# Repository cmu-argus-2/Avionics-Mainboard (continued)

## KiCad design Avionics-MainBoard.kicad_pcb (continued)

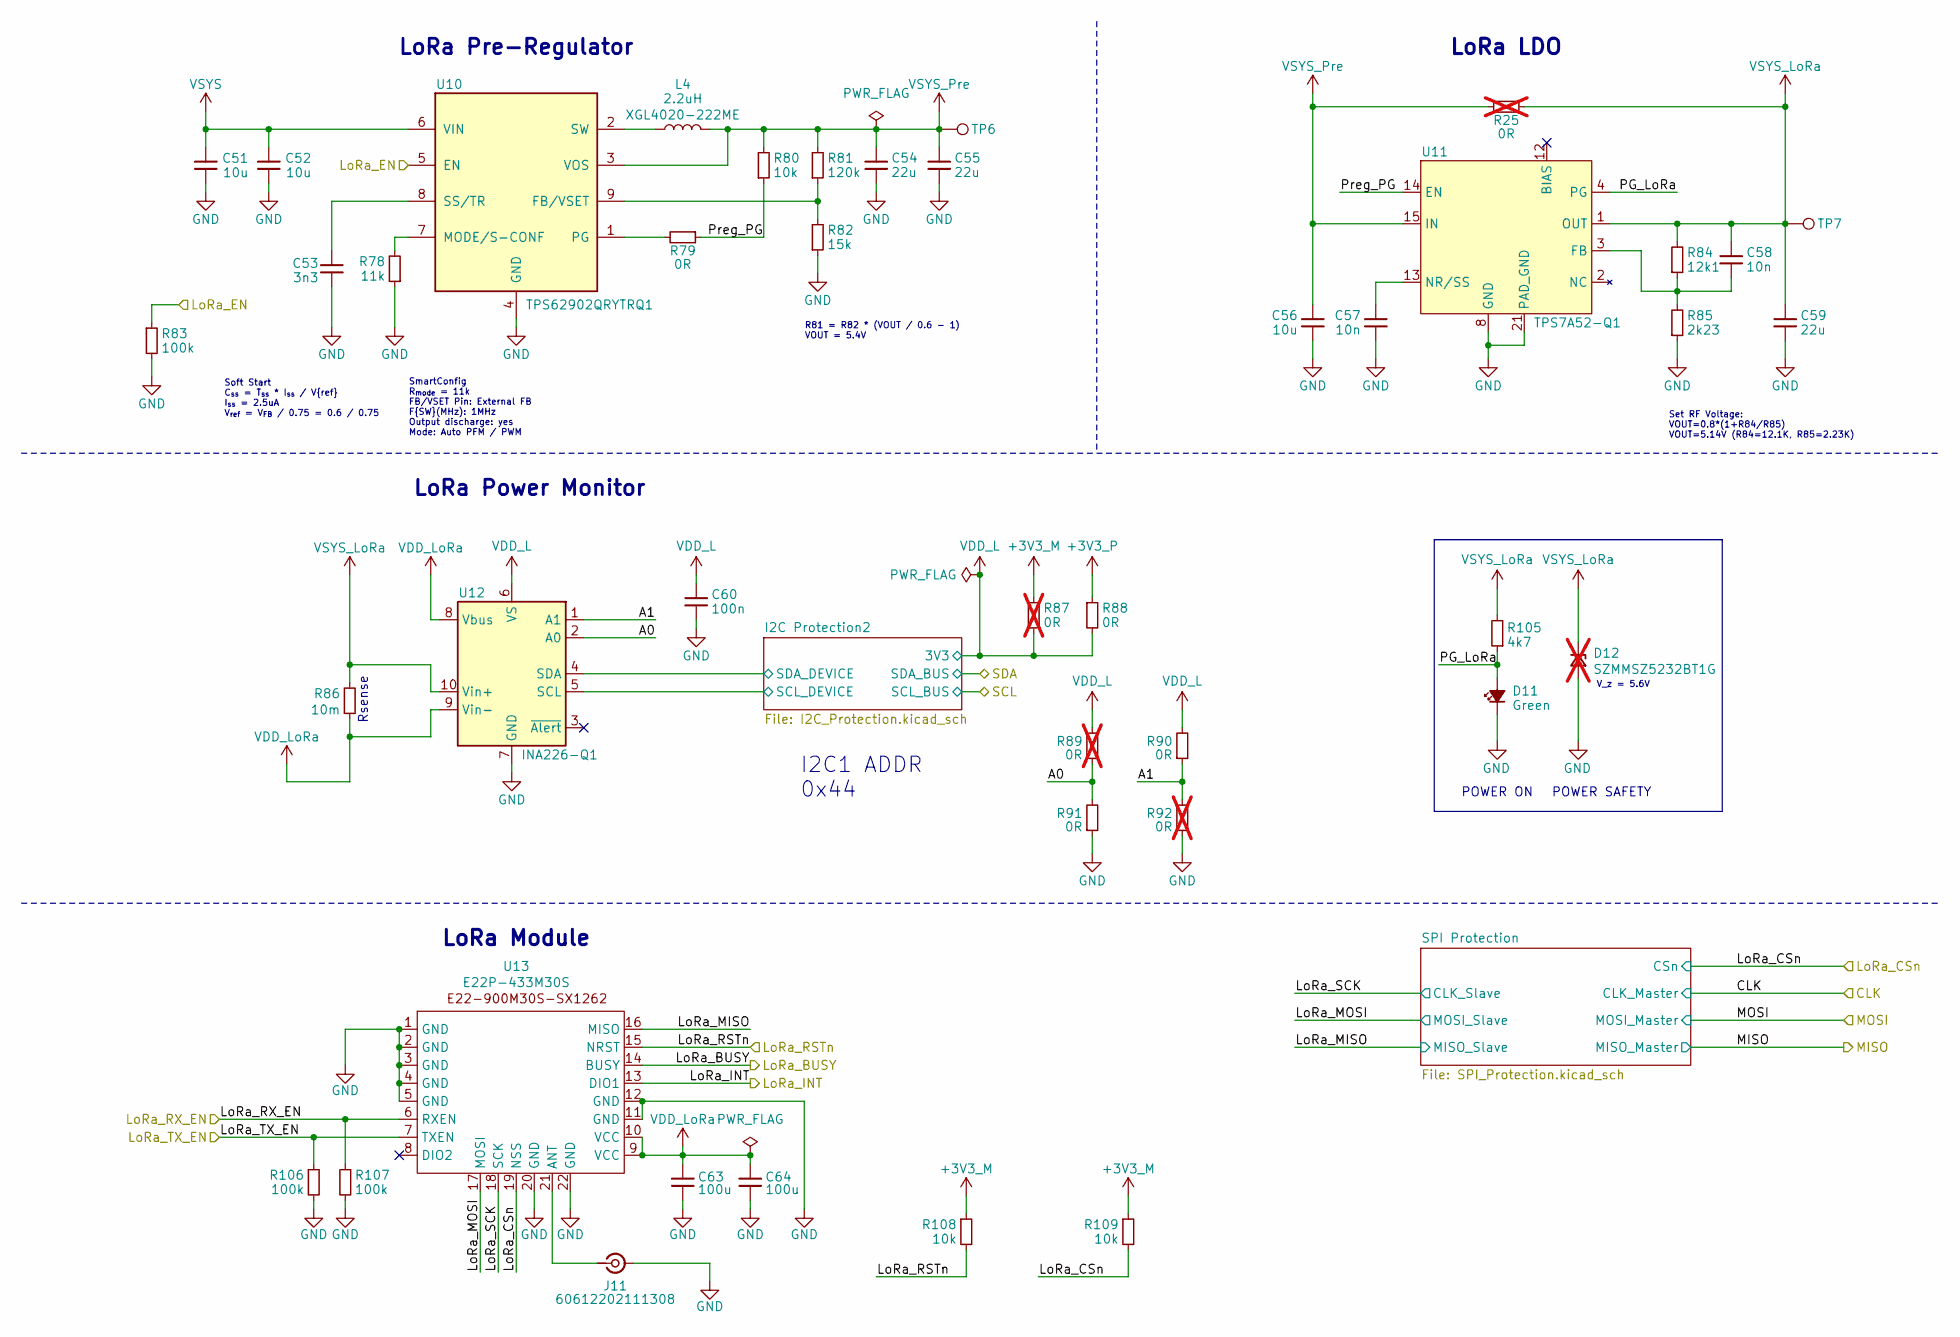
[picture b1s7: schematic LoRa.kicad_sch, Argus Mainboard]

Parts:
C51, C52: 10u; C_0805_2012Metric; MPN C386084
C53: 3n3; C_0603_1608Metric; MPN C3877267
C54, C55, C59: 22u; C_1210_3225Metric; MPN C2803395
C56: 10u; C_0805_2012Metric; MPN C2803395
C57, C58: 10n; C_0603_1608Metric; MPN C2803395
C60: 100n; C_0603_1608Metric; MPN C2803395
C63: 100u; C_1210_3225Metric; MPN C2214844
C64: 100u; C_1210_3225Metric; MPN C386084
D11: LED_G_0603_LTST-C190GKT; LED_0603_1608Metric; MPN C2909774
D12: SZMMSZ5232BT1G; D_SOD-123; not fitted
J11: 60612202111308; MPN C88374
L4: 2.2uH; L_Coilcraft_XAL4020-XXX
R25: 0R; R_0603_1608Metric; MPN C844759; not fitted
R78: 11k; R_0603_1608Metric; MPN C844759
R79: 0R; R_0603_1608Metric; MPN C844759
R80: 10k; R_0603_1608Metric; MPN C844759
R81: 120k; R_0603_1608Metric; MPN C844759
R82: 15k; R_0603_1608Metric; MPN C844759
R83: 100k; R_0603_1608Metric; MPN C237792
R84: 12k1; R_0603_1608Metric; MPN C844759
R85: 2k23; R_0603_1608Metric; MPN C844759
R86: 10m; R_1206_3216Metric; MPN C840621
R87: 0R; R_0603_1608Metric; MPN C237792; not fitted
R88: 0R; R_0603_1608Metric; MPN C237792
R89, R92: 0R; R_0603_1608Metric; MPN C844915; not fitted
R90, R91: 0R; R_0603_1608Metric; MPN C844915
R105: 4k7; R_0603_1608Metric; MPN C844931
R106, R107: 100k; R_0603_1608Metric; MPN C2479067
R108, R109: 10k; R_0603_1608Metric; MPN C2479067
TP6, TP7: TestPoint; TestPoint_Pad_D1.5mm
U10: TPS62902QRYTRQ1
U11: TPS7A52-Q1; TPS7A5201Q
U12: INA226-Q1; TSSOP-10_3x3mm_P0.5mm
U13: E22P-433M30S; E22-900M30S-SX1262

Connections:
+3V3_M: R87.1, R108.1, R109.1; also elsewhere on the board
+3V3_P: R88.1; also elsewhere on the board
/LoRa/A0: R89.1, R91.2, U12.2 (A0)
/LoRa/A1: R90.1, R92.2, U12.1 (A1)
/LoRa/I2C Protection2/SCL_DEVICE: U12.5 (SCL); also elsewhere on the board
/LoRa/I2C Protection2/SDA_DEVICE: U12.4 (SDA); also elsewhere on the board
/LoRa/LoRa_BUSY: U13.14 (BUSY); also elsewhere on the board
/LoRa/LoRa_CSn: R109.2, U13.19 (NSS); also elsewhere on the board
/LoRa/LoRa_INT: U13.13 (DIO1); also elsewhere on the board
/LoRa/LoRa_MISO: U13.16 (MISO); also elsewhere on the board
/LoRa/LoRa_MOSI: U13.17 (MOSI); also elsewhere on the board
/LoRa/LoRa_RSTn: R108.2, U13.15 (NRST); also elsewhere on the board
/LoRa/LoRa_RX_EN: R107.1, U13.6 (RXEN); also elsewhere on the board
/LoRa/LoRa_SCK: U13.18 (SCK); also elsewhere on the board
/LoRa/LoRa_TX_EN: R106.1, U13.7 (TXEN); also elsewhere on the board
/LoRa/PG_LoRa: D11.2 (A), R105.1, U11.4 (PG)
/LoRa/Preg_PG: R79.1, R80.1, U11.14 (EN)
/MCU_IO/LoRa_EN: R83.1, U10.5 (EN); also elsewhere on the board
GND: C51.2, C52.2, C53.1, C54.1, C55.1, C56.1, C57.1, C59.1, C60.1, C63.1, C64.1, D11.1 (K), D12.2 (A), J11.2 (Ext), R78.1, R82.1, R83.2, R85.1, R91.1, R92.1, R106.2, R107.2, U10.4 (GND), U11.8 (GND), U11.18 (GND), U11.21 (PAD_GND), U12.7 (GND), U13.1 (GND), U13.2 (GND), U13.3 (GND), U13.4 (GND), U13.5 (GND), U13.11 (GND), U13.12 (GND), U13.20 (GND), U13.22 (GND); also elsewhere on the board
unnamed: J11.1 (In), U13.21 (ANT)
unnamed: R81.1, R82.2, U10.9 (FB/VSET)
unnamed: R78.2, U10.7 (MODE/S-CONF)
unnamed: R79.2, U10.1 (PG)
unnamed: C53.2, U10.8 (SS/TR)
unnamed: L4.1, U10.2 (SW)
unnamed: C58.1, R84.1, R85.2, U11.3 (FB)
unnamed: C57.2, U11.13 (NR/SS)
VDD_L: C60.2, R87.2, R88.2, R89.2, R90.2, U12.6 (VS); also elsewhere on the board
VDD_LoRa: C63.2, C64.2, R86.1, U12.8 (Vbus), U12.9 (Vin-), U13.9 (VCC), U13.10 (VCC)
VSYS: C51.1, C52.1, U10.6 (VIN); also elsewhere on the board
VSYS_LoRa: C58.2, C59.2, D12.1 (K), R25.1, R84.2, R86.2, R105.2, TP7.1 (1_1), U11.1 (OUT), U11.19 (OUT), U11.20 (OUT), U12.10 (Vin+)
VSYS_Pre: C54.2, C55.2, C56.2, L4.2, R25.2, R80.2, R81.2, TP6.1 (1_1), U10.3 (VOS), U11.15 (IN), U11.16 (IN), U11.17 (IN)

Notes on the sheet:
I2C1 ADDR 0x44
R81 = R82 * (VOUT / 0.6 - 1) VOUT = 5.4V
LoRa Module
LoRa Pre-Regulator
POWER ON
Set RF Voltage: VOUT=0.8*(1+R84/R85) VOUT=5.14V (R84=12.1K, R85=2.23K)
SmartConfig R_{mode} = 11k FB/VSET Pin: External FB F{SW}(MHz): 1MHz Output discharge: yes Mode: Auto PFM / PWM
LoRa Power Monitor
V_z = 5.6V
LoRa LDO
Soft Start C_{ss} = T_{ss} * I_{ss} / V{ref} I_{ss} = 2.5uA V_{ref} = V_{FB} / 0.75 = 0.6 / 0.75
POWER SAFETY
Rsense

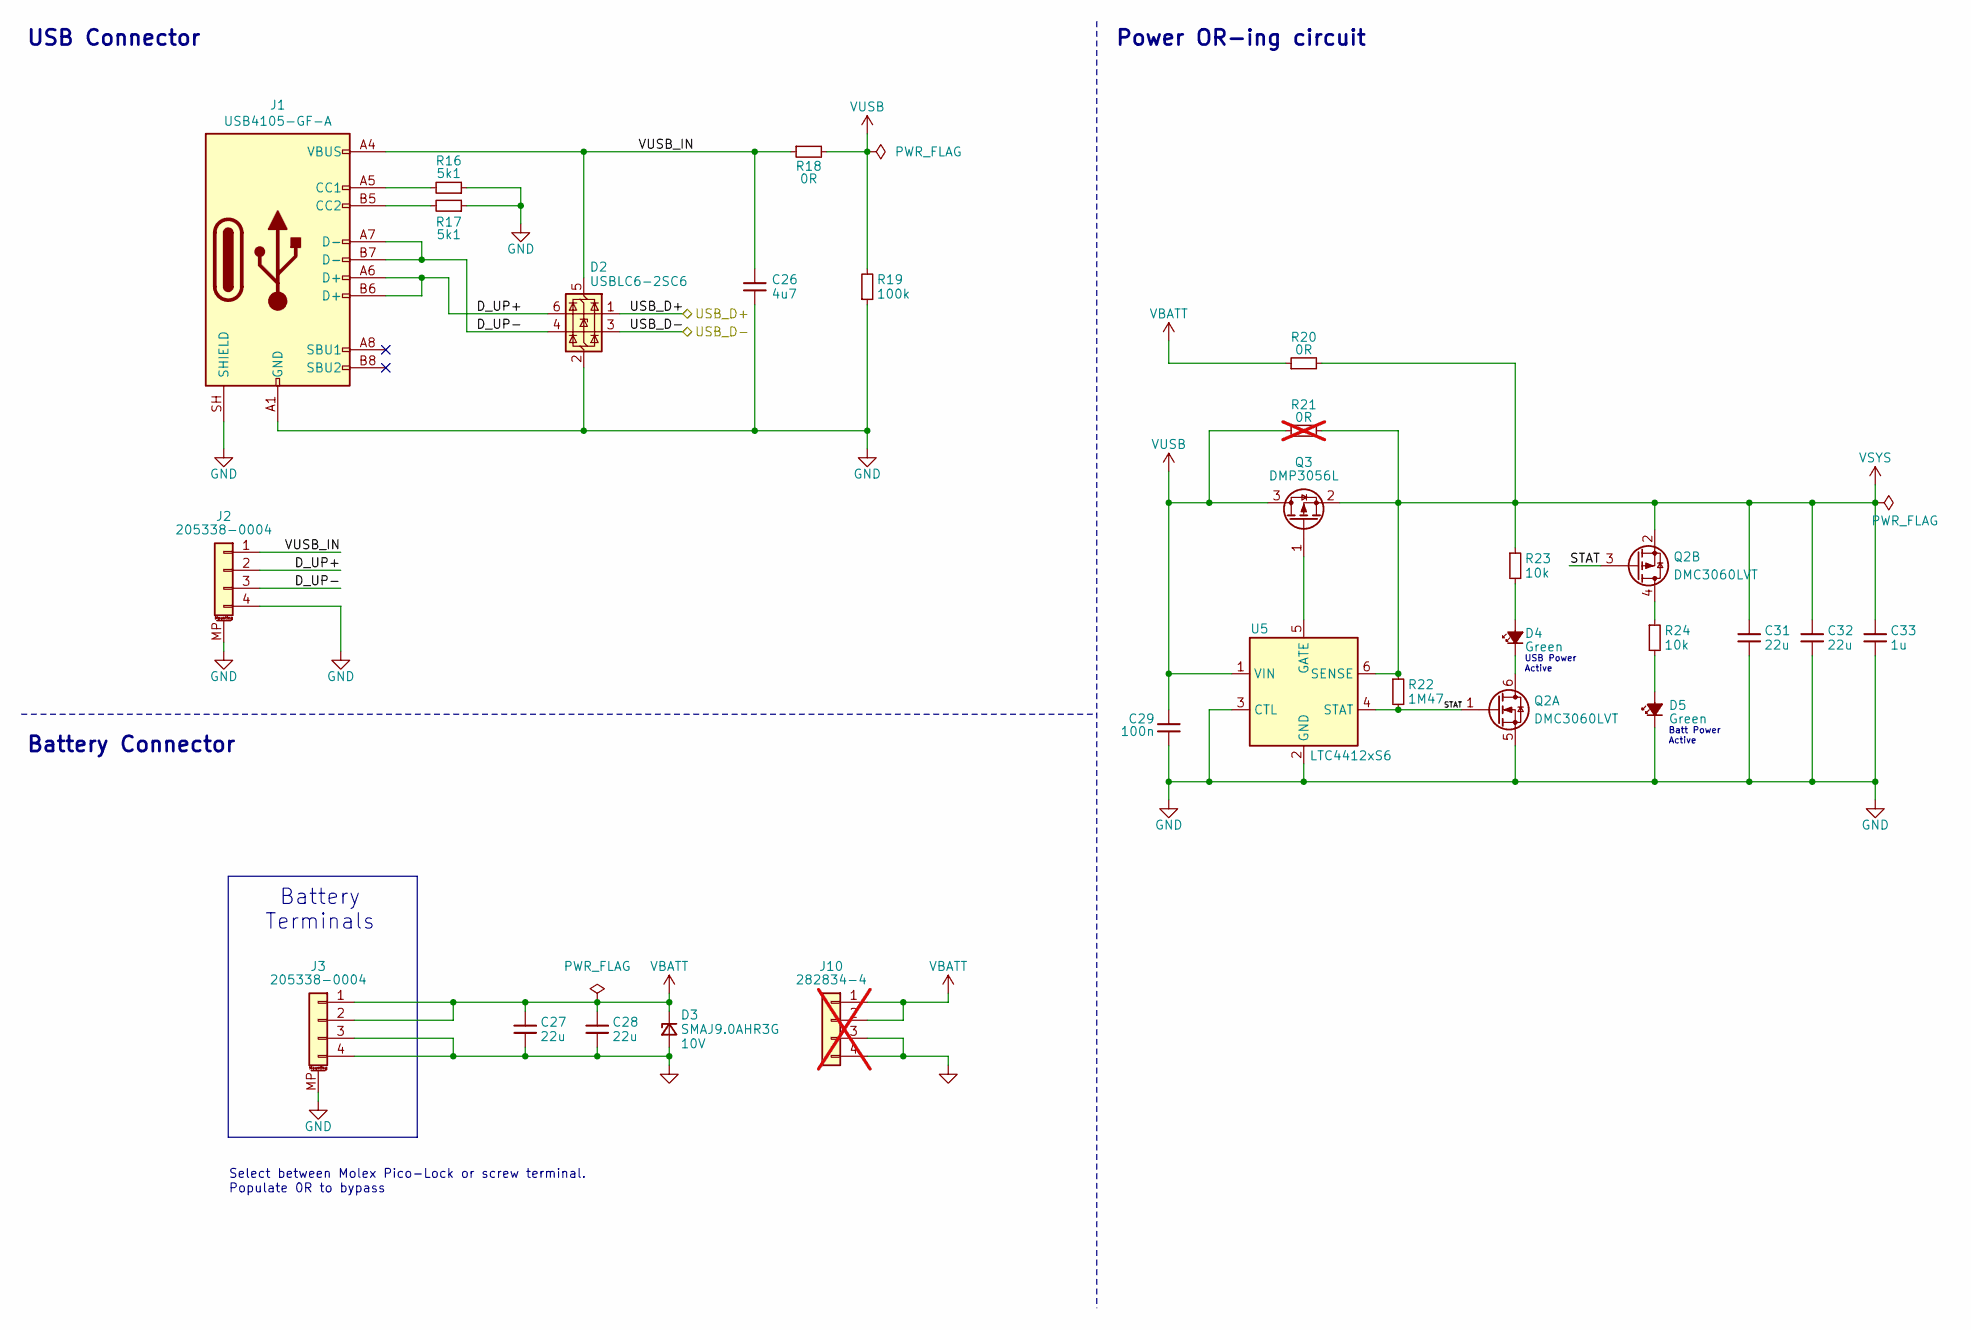
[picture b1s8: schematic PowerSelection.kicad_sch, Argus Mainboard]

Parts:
C26: 4u7; C_0805_2012Metric; MPN C3861036
C27, C28, C31, C32: 22u; C_1210_3225Metric; MPN C2803395
C29: 100n; C_0603_1608Metric; MPN C386084
C33: 1u; C_0603_1608Metric; MPN C2214844
D2: USBLC6-2SC6; SOT-23-6; MPN C7519
D3: SMAJ9.0AHR3G; D_SMA; Part 10V
D4, D5: LED_G_0603_LTST-C190GKT; LED_0603_1608Metric; MPN C2909774
J1: USB4105-GF-A; USB_C_Receptacle_GCT_USB4105-xx-A_16P_TopMnt_Horizontal; MPN C3020560
J2, J3: 205338-0004; Molex_Pico-Lock_205338-0004_1x04-1MP_P2.00mm_Horizontal; MPN C916325
J10: 282834-4; TE_282834-4; not fitted
Q2: DMC3060LVT; TSOT-23-6
Q3: DMP3056L; SOT-23
R16, R17: 5k1; R_0603_1608Metric; MPN C2484686
R18, R20: 0R; R_0603_1608Metric; MPN C844915
R19: 100k; R_0603_1608Metric; MPN C2479067
R21: 0R; R_0603_1608Metric; MPN C844915; not fitted
R22: 1M47; R_0603_1608Metric; MPN C237792
R23, R24: 10k; R_0603_1608Metric; MPN C237792
U5: LTC4412xS6; TSOT-23-6

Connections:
/Power Selection/D_UP+: D2.6 (I/O1), J1.A6 (D+), J1.B6 (D+), J2.2
/Power Selection/D_UP-: D2.4 (I/O2), J1.A7 (D-), J1.B7 (D-), J2.3
/Power Selection/STAT: Q2.1 (G), Q2.3 (G), R22.2, U5.4 (STAT)
/Power Selection/USB_D+: D2.1 (I/O1); also elsewhere on the board
/Power Selection/USB_D-: D2.3 (I/O2); also elsewhere on the board
/Power Selection/VUSB_IN: C26.1, D2.5 (VBUS), J1.A4 (VBUS), J1.A9 (VBUS), J1.B4 (VBUS), J1.B9 (VBUS), J2.1, R18.1
GND: C26.2, C27.2, C28.2, C29.1, C31.1, C32.1, C33.2, D2.2 (GND), D3.2 (A), D5.1 (K), J1.A1 (GND), J1.A12 (GND), J1.B1 (GND), J1.B12 (GND), J1.SH (SHIELD), J2.4, J2.MP (MountPin), J3.3, J3.4, J3.MP (MountPin), J10.3, J10.4, Q2.5 (S), R16.1, R17.1, R19.1, U5.2 (GND), U5.3 (CTL); also elsewhere on the board
unnamed: D4.2 (A), R23.2
unnamed: D4.1 (K), Q2.6 (D)
unnamed: D5.2 (A), R24.2
unnamed: J1.A5 (CC1), R16.2
unnamed: J1.B5 (CC2), R17.2
unnamed: Q2.4 (D), R24.1
unnamed: Q3.1 (G), U5.5 (GATE)
VBATT: C27.1, C28.1, D3.1 (K), J3.1, J3.2, J10.1, J10.2, R20.1; also elsewhere on the board
VSYS: C31.2, C32.2, C33.1, Q2.2 (S), Q3.2 (S), R20.2, R21.2, R22.1, R23.1, U5.6 (SENSE); also elsewhere on the board
VUSB: C29.2, Q3.3 (D), R18.2, R19.2, R21.1, U5.1 (VIN)

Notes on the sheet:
Batt Power Active
Power OR-ing circuit
Battery Connector
Select between Molex Pico-Lock or screw terminal. Populate 0R to bypass
USB Power Active
USB Connector
Battery Terminals

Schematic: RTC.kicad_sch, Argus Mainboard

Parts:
BT2: BAT-HLD-012-SMT; BatteryHolder_LINX_BAT-HLD-012-SMT; MPN C5189234
C75, C76: 10u; C_0805_2012Metric; MPN C307348
C77, C78: 100n; C_0603_1608Metric; MPN C307348
D16: LED_G_0603_LTST-C190GKT; LED_0603_1608Metric; MPN C2909774
R138, R140: 0R; R_0603_1608Metric; not fitted
R139: 0R; R_0603_1608Metric
R141, R144: 100k; R_0603_1608Metric
R142: 2k7; R_0603_1608Metric; MPN C237112
R143: 10k; R_0603_1608Metric
R185: 10k; R_0603_1608Metric; MPN C237112
TP8: TestPoint; TestPoint_Pad_D1.5mm
U17: TPS22917DBV; SOT-23-6
U18: RV-3032-C7; IC_RV-3032-C7-32.768KHZ-2.5PPM-TA-QC

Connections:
+3V3_M: R138.1, R143.1; also elsewhere on the board
+3V3_P: R139.1; also elsewhere on the board
+3V3_RTC: C76.1, C77.1, R140.1, R142.2, R185.2, U17.6 (VOUT), U18.6 (VDD); also elsewhere on the board
/MCU_IO/RTC_EN: R141.1, U17.3 (ON); also elsewhere on the board
/MCU_IO/RTC_INT: R143.2, U18.3 (~INT); also elsewhere on the board
/RTC/EVI: R144.1, U18.4 (EVI)
/RTC/RTC_SCL: U18.8 (SCL); also elsewhere on the board
/RTC/RTC_SDA: U18.2 (SDA); also elsewhere on the board
GND: BT2.2 (-), C75.2, C76.2, C77.2, C78.2, D16.1 (K), R141.2, R144.2, U17.2 (GND), U18.5 (VSS); also elsewhere on the board
unnamed: BT2.1 (+), C78.1, U18.1 (VBACKUP)
unnamed: D16.2 (A), R142.1
unnamed: R185.1, U17.5 (QOD)
unnamed: C75.1, R138.2, R139.2, R140.2, U17.1 (VIN)
unnamed: TP8.1 (1_1), U18.7 (CLKOUT)

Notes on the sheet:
RTC Enable
I2C1 ADDR 0x51
RTC

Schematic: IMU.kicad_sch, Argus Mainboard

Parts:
C81, C82, C83, C85, C86: 10u; C_0805_2012Metric; MPN C307348
C84: 1u; C_0603_1608Metric; MPN C307348
C87, C88: 100n; C_0603_1608Metric; MPN C307348
D17, D18: LED_G_0603_LTST-C190GKT; LED_0603_1608Metric; MPN C2909774
R157, R159, R169, R171: 0R; R_0603_1608Metric; not fitted
R158, R170: 0R; R_0603_1608Metric
R160, R172: 100k; R_0603_1608Metric
R161, R173: 2k7; R_0603_1608Metric; MPN C237112
R162, R174: 10k; R_0603_1608Metric; MPN C2479067
R163, R175, R176: 100k; R_0603_1608Metric; MPN C2479067
R183, R184: 10k; R_0603_1608Metric; MPN C237112
U19, U21: TPS22917DBV; SOT-23-6
U20: MMC5983MA; LGA-16_3x3mm_P0.5mm
U22: ASM330LHHG1TR; LGA-14_3x2.5mm_P0.5mm_LayoutBorder3x4y

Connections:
+3V3_IMU: C86.1, C87.1, C88.1, R171.1, R173.2, R174.2, R184.2, U21.6 (VOUT), U22.5 (VDDIO), U22.8 (VDD)
+3V3_M: R157.1, R169.1; also elsewhere on the board
+3V3_MAG: C82.1, C84.1, R159.1, R161.2, R162.2, R183.2, U19.6 (VOUT), U20.2 (VDD), U20.13 (VDDIO)
+3V3_P: R158.1, R170.1; also elsewhere on the board
/IMU/IMU_CSn: R174.1, U22.12 (CS); also elsewhere on the board
/IMU/IMU_INT1: R175.2, U22.4 (INT1); also elsewhere on the board
/IMU/IMU_INT2: R176.2, U22.9 (INT2); also elsewhere on the board
/IMU/IMU_MISO: U22.1 (SDO/SA0); also elsewhere on the board
/IMU/IMU_MOSI: U22.14 (SDA); also elsewhere on the board
/IMU/IMU_SCK: U22.13 (SCL); also elsewhere on the board
/IMU/Mag_CSn: R162.1, U20.4 (CS); also elsewhere on the board
/IMU/Mag_INT: R163.1, U20.15 (INT); also elsewhere on the board
/IMU/Mag_MISO: U20.5 (MISO); also elsewhere on the board
/IMU/Mag_MOSI: U20.16 (MOSI); also elsewhere on the board
/IMU/Mag_SCK: U20.1 (SCK); also elsewhere on the board
/MCU_IO/IMU_EN: R172.1, U21.3 (ON); also elsewhere on the board
/MCU_IO/Mag_EN: R160.1, U19.3 (ON); also elsewhere on the board
GND: C81.2, C82.2, C83.2, C84.2, C85.2, C86.2, C87.2, C88.2, D17.1 (K), D18.1 (K), R160.2, R163.2, R172.2, R175.1, R176.1, U19.2 (GND), U20.9 (GND), U20.11 (GND), U21.2 (GND), U22.2 (SDx), U22.3 (SCx), U22.6 (GND), U22.7 (GND); also elsewhere on the board
unnamed: D17.2 (A), R161.1
unnamed: D18.2 (A), R173.1
unnamed: R183.1, U19.5 (QOD)
unnamed: C81.1, R157.2, R158.2, R159.2, U19.1 (VIN)
unnamed: C83.1, U20.10 (CAP)
unnamed: R184.1, U21.5 (QOD)
unnamed: C85.1, R169.2, R170.2, R171.2, U21.1 (VIN)

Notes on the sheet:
Magnetometer
6-DoF IMU (Accelerometer + Gyroscope)

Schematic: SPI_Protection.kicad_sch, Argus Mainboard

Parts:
Q24: MMBT2907; SOT-23; MPN C5354954
R164: 4k7; R_0603_1608Metric; MPN C844931
R165: 0R; R_0603_1608Metric; MPN C844915
R166, R167: 1k; R_0603_1608Metric; MPN C2484712
R168: 0R; R_0603_1608Metric; not fitted

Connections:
/IMU/CLK: R166.2; also elsewhere on the board
/IMU/MISO: Q24.3 (C), R168.1; also elsewhere on the board
/IMU/MOSI: R167.2; also elsewhere on the board
/IMU/Mag_CSn: R164.2; also elsewhere on the board
/IMU/Mag_MISO: R165.2, R168.2; also elsewhere on the board
/IMU/Mag_MOSI: R167.1; also elsewhere on the board
/IMU/Mag_SCK: R166.1; also elsewhere on the board
unnamed: Q24.1 (B), R164.1
unnamed: Q24.2 (E), R165.1

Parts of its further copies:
Q18, Q19, Q25: MMBT2907; SOT-23; MPN C5354954
R110, R133, R177: 4k7; R_0603_1608Metric; MPN C844931
R111, R134, R178: 0R; R_0603_1608Metric; MPN C844915
R112, R113, R135, R136, R179, R180: 1k; R_0603_1608Metric; MPN C2484712
R114, R137, R181: 0R; R_0603_1608Metric; not fitted

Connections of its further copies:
/IMU/CLK: R112.2, R135.2, R179.2; also elsewhere on the board
/IMU/IMU_CSn: R177.2; also elsewhere on the board
/IMU/IMU_MISO: R178.2, R181.2; also elsewhere on the board
/IMU/IMU_MOSI: R180.1; also elsewhere on the board
/IMU/IMU_SCK: R179.1; also elsewhere on the board
/IMU/MISO: Q18.3 (C), Q19.3 (C), Q25.3 (C), R114.1, R137.1, R181.1; also elsewhere on the board
/IMU/MOSI: R113.2, R136.2, R180.2; also elsewhere on the board
/LoRa/LoRa_CSn: R110.2; also elsewhere on the board
/LoRa/LoRa_MISO: R111.2, R114.2; also elsewhere on the board
/LoRa/LoRa_MOSI: R113.1; also elsewhere on the board
/LoRa/LoRa_SCK: R112.1; also elsewhere on the board
/MCU_IO/SD_CSn: R133.2; also elsewhere on the board
/SD/SD_CLK: R135.1; also elsewhere on the board
/SD/SD_MISO: R134.2, R137.2; also elsewhere on the board
/SD/SD_MOSI: R136.1; also elsewhere on the board
unnamed: Q18.1 (B), R110.1
unnamed: Q18.2 (E), R111.1
unnamed: Q19.1 (B), R133.1
unnamed: Q19.2 (E), R134.1
unnamed: Q25.1 (B), R177.1
unnamed: Q25.2 (E), R178.1

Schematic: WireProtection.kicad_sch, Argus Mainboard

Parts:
C40: 10n; C_0603_1608Metric; MPN C161232
Q4: MBT2222ADW1T1; SOT-363_SC-70-6; Manufacturer_Part_Number MBT2222ADW1T1G
Q5: NX3008NBKS; SOT-363_SC-70-6; MPN C3280240
R36, R37: 10k; R_0603_1608Metric; MPN C2479067
R38: 680R; R_0603_1608Metric; MPN C844802
R39: 100k; R_0603_1608Metric; MPN C237792
R40: 200k; R_0603_1608Metric; MPN C118142
R41: 0R; R_0603_1608Metric; not fitted

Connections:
/MCU_IO/I2C0_SCL: Q4.1 (E1), Q4.3 (C2), R41.2; also elsewhere on the board
/Main Power/I2C Protection/SCL_DEVICE: Q4.4 (E2), Q4.6 (C1), R37.2, R40.1, R41.1; also elsewhere on the board
GND: C40.2, Q5.1 (S), Q5.4 (S); also elsewhere on the board
unnamed: Q4.2 (B1), R38.1
unnamed: Q4.5 (B2), Q5.6 (D), R36.2, R38.2
unnamed: Q5.2 (G), Q5.3 (D), R39.2
unnamed: C40.1, Q5.5 (G), R40.2
VDD_M: R36.1, R37.1, R39.1; also elsewhere on the board

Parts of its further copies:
C41, C48, C49, C61, C62, C79, C80: 10n; C_0603_1608Metric; MPN C161232
Q6, Q8, Q10, Q14, Q16, Q20, Q22: MBT2222ADW1T1; SOT-363_SC-70-6; Manufacturer_Part_Number MBT2222ADW1T1G
Q7, Q9, Q11, Q15, Q17, Q21, Q23: NX3008NBKS; SOT-363_SC-70-6; MPN C3280240
R42, R43, R58, R59, R64, R65, R93, R94, R99, R100, R145, R146, R151, R152: 10k; R_0603_1608Metric; MPN C2479067
R44, R60, R66, R95, R101, R147, R153: 680R; R_0603_1608Metric; MPN C844802
R45, R61, R67, R96, R102, R148, R154: 100k; R_0603_1608Metric; MPN C237792
R46, R62, R68, R97, R103, R149, R155: 200k; R_0603_1608Metric; MPN C118142
R47, R63, R69, R98, R104, R150, R156: 0R; R_0603_1608Metric; not fitted

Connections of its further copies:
+3V3_RTC: R145.1, R146.1, R148.1, R151.1, R152.1, R154.1; also elsewhere on the board
/LoRa/I2C Protection2/SCL_DEVICE: Q14.4 (E2), Q14.6 (C1), R94.2, R97.1, R98.1; also elsewhere on the board
/LoRa/I2C Protection2/SDA_DEVICE: Q16.4 (E2), Q16.6 (C1), R100.2, R103.1, R104.1; also elsewhere on the board
/MCU_IO/I2C0_SCL: Q8.1 (E1), Q8.3 (C2), Q14.1 (E1), Q14.3 (C2), Q20.1 (E1), Q20.3 (C2), R63.2, R98.2, R150.2; also elsewhere on the board
/MCU_IO/I2C0_SDA: Q6.1 (E1), Q6.3 (C2), Q10.1 (E1), Q10.3 (C2), Q16.1 (E1), Q16.3 (C2), Q22.1 (E1), Q22.3 (C2), R47.2, R69.2, R104.2, R156.2; also elsewhere on the board
/Main Power/I2C Protection1/SCL_DEVICE: Q8.4 (E2), Q8.6 (C1), R59.2, R62.1, R63.1; also elsewhere on the board
/Main Power/I2C Protection1/SDA_DEVICE: Q10.4 (E2), Q10.6 (C1), R65.2, R68.1, R69.1; also elsewhere on the board
/Main Power/I2C Protection/SDA_DEVICE: Q6.4 (E2), Q6.6 (C1), R43.2, R46.1, R47.1; also elsewhere on the board
/RTC/RTC_SCL: Q20.4 (E2), Q20.6 (C1), R146.2, R149.1, R150.1; also elsewhere on the board
/RTC/RTC_SDA: Q22.4 (E2), Q22.6 (C1), R152.2, R155.1, R156.1; also elsewhere on the board
GND: C41.2, C48.2, C49.2, C61.2, C62.2, C79.2, C80.2, Q7.1 (S), Q7.4 (S), Q9.1 (S), Q9.4 (S), Q11.1 (S), Q11.4 (S), Q15.1 (S), Q15.4 (S), Q17.1 (S), Q17.4 (S), Q21.1 (S), Q21.4 (S), Q23.1 (S), Q23.4 (S); also elsewhere on the board
unnamed: Q6.2 (B1), R44.1
unnamed: Q6.5 (B2), Q7.6 (D), R42.2, R44.2
unnamed: Q7.2 (G), Q7.3 (D), R45.2
unnamed: C41.1, Q7.5 (G), R46.2
unnamed: Q8.2 (B1), R60.1
unnamed: Q8.5 (B2), Q9.6 (D), R58.2, R60.2
unnamed: Q9.2 (G), Q9.3 (D), R61.2
unnamed: C48.1, Q9.5 (G), R62.2
unnamed: Q10.2 (B1), R66.1
unnamed: Q10.5 (B2), Q11.6 (D), R64.2, R66.2
unnamed: Q11.2 (G), Q11.3 (D), R67.2
unnamed: C49.1, Q11.5 (G), R68.2
unnamed: Q14.2 (B1), R95.1
unnamed: Q14.5 (B2), Q15.6 (D), R93.2, R95.2
unnamed: Q15.2 (G), Q15.3 (D), R96.2
unnamed: C61.1, Q15.5 (G), R97.2
unnamed: Q16.2 (B1), R101.1
unnamed: Q16.5 (B2), Q17.6 (D), R99.2, R101.2
unnamed: Q17.2 (G), Q17.3 (D), R102.2
unnamed: C62.1, Q17.5 (G), R103.2
unnamed: Q20.2 (B1), R147.1
unnamed: Q20.5 (B2), Q21.6 (D), R145.2, R147.2
unnamed: Q21.2 (G), Q21.3 (D), R148.2
unnamed: C79.1, Q21.5 (G), R149.2
unnamed: Q22.2 (B1), R153.1
unnamed: Q22.5 (B2), Q23.6 (D), R151.2, R153.2
unnamed: Q23.2 (G), Q23.3 (D), R154.2
unnamed: C80.1, Q23.5 (G), R155.2
VDD_L: R93.1, R94.1, R96.1, R99.1, R100.1, R102.1; also elsewhere on the board
VDD_M: R42.1, R43.1, R45.1; also elsewhere on the board
VDD_P: R58.1, R59.1, R61.1, R64.1, R65.1, R67.1; also elsewhere on the board

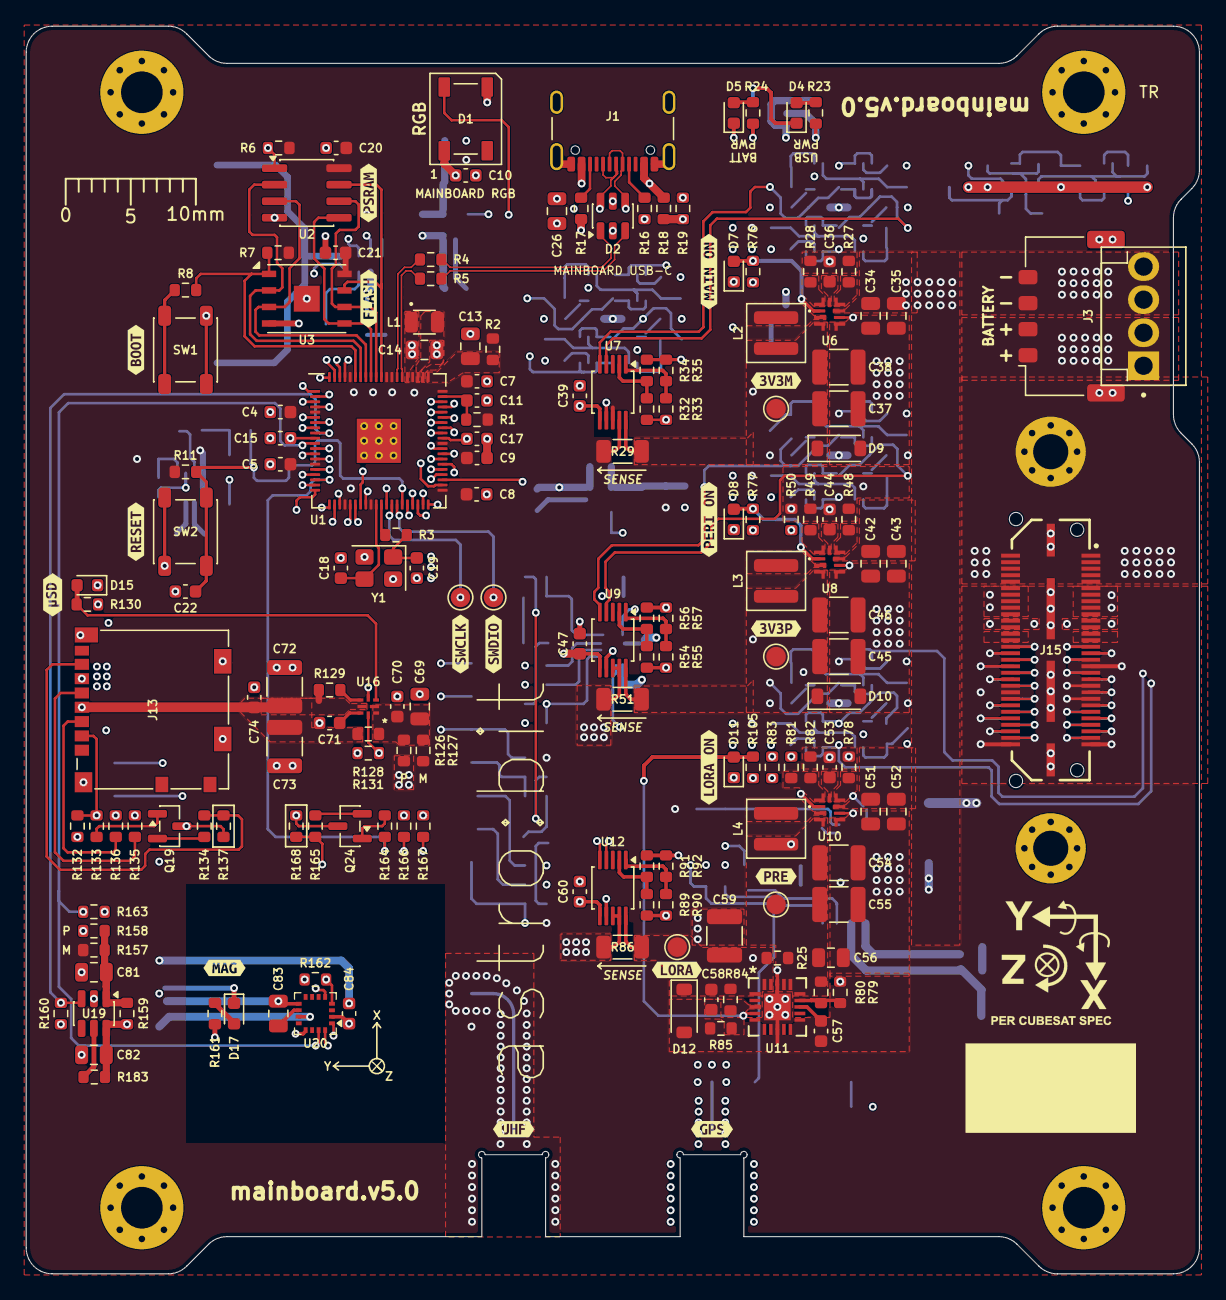
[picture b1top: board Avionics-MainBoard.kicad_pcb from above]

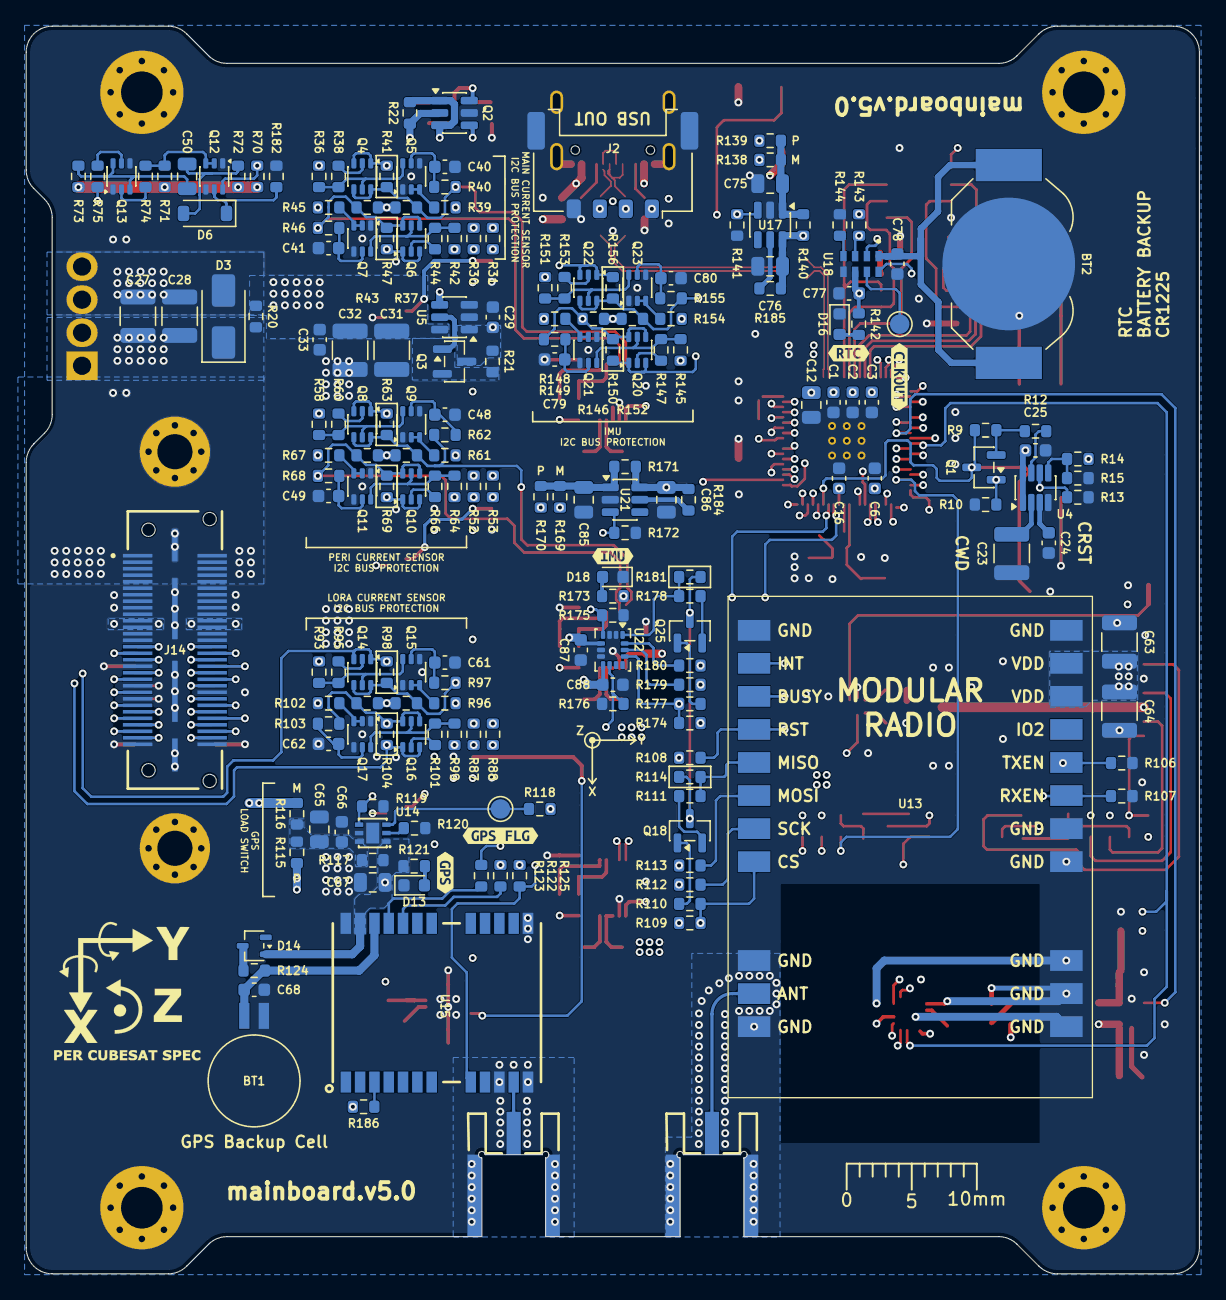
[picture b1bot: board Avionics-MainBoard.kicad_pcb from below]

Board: 4 copper layers, 90.2 x 95.9 mm, 391 parts (202 on the bottom side), 230 nets.

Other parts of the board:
kibuzzard-6A94A6EB: G***; kibuzzard-6A94A6EB
kibuzzard-6A94A6F2: G***; kibuzzard-6A94A6F2
kibuzzard-6A94A9F0: G***; kibuzzard-6A94A9F0
kibuzzard-6A94A74C: G***; kibuzzard-6A94A74C
kibuzzard-6A94A84D: G***; kibuzzard-6A94A84D
kibuzzard-6A94A845: G***; kibuzzard-6A94A845
kibuzzard-6A94A973: G***; kibuzzard-6A94A973
kibuzzard-6A94AA08: G***; kibuzzard-6A94AA08
kibuzzard-6A94AA93: G***; kibuzzard-6A94AA93
kibuzzard-6A94AAA8: G***; kibuzzard-6A94AAA8
kibuzzard-6A94AF59: G***; kibuzzard-6A94AF59
kibuzzard-6A94B7E3: G***; kibuzzard-6A94B7E3
kibuzzard-6A94B390: G***; kibuzzard-6A94B390
kibuzzard-6A94B568: G***; kibuzzard-6A94B568
kibuzzard-6A94B807: G***; kibuzzard-6A94B807
kibuzzard-67C0A908: G***; kibuzzard-67C0A908
kibuzzard-67C0B8D2: G***; kibuzzard-67C0B8D2
kibuzzard-67C0B8E2: G***; kibuzzard-67C0B8E2
kibuzzard-67C0B43D: G***; kibuzzard-67C0B43D
kibuzzard-67C0B44F: G***; kibuzzard-67C0B44F
kibuzzard-67C0B466: G***; kibuzzard-67C0B466
kibuzzard-67C0B482: G***; kibuzzard-67C0B482

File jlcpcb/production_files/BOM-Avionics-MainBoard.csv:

Comment,Designator,Footprint,LCSC,Quantity
0R,"R111,R115,R12,R122,R123,R126,R134,R139,R14,R158,R165,R170,R178,R18,R186,R20,R31,R34,R35,R53,R54,R57,R79,R88,R90,R91",R_0603_1608Metric,C2441282,26
100k,"R10,R102,R106,R107,R119,R129,R131,R141,R144,R148,R154,R160,R163,R172,R175,R176,R182,R19,R39,R45,R50,R61,R67,R71,R73,R83,R96",R_0603_1608Metric,C237792,27
100n,"C1,C10,C15,C16,C17,C2,C20,C21,C25,C29,C3,C39,C4,C47,C5,C6,C60,C66,C7,C74,C77,C78,C8,C87,C88,C9",C_0603_1608Metric,C15725,26
100n,C23,C_1210_3225Metric,C2179848,1
100u,"C63,C64",C_1210_3225Metric,C394395,2
104031-0811,J13,microSD_HC_Molex_104031-0811,C585350,1
10R,R2,R_0603_1608Metric,C2479145,1
10k,"R100,R108,R109,R11,R118,R125,R13,R132,R143,R145,R146,R151,R152,R162,R174,R183,R184,R185,R23,R24,R36,R37,R42,R43,R58,R59,R6,R64,R65,R7,R75,R80,R93,R94,R99",R_0603_1608Metric,C2479067,35
10m,"R29,R51,R86",R_1206_3216Metric,C844280,3
10n,"C24,C40,C41,C48,C49,C57,C58,C61,C62,C79,C80",C_0603_1608Metric,C1589,11
10u,"C34,C35,C42,C43,C50,C51,C52,C56,C65,C67,C69,C75,C76,C81,C82,C83,C85,C86",C_0805_2012Metric,C15850,18
11k,R78,R_0603_1608Metric,C2479538,1
120k,R81,R_0603_1608Metric,C844735,1
12k1,R84,R_0603_1608Metric,C2483996,1
15k,R82,R_0603_1608Metric,C6112657,1
15p,"C18,C19",C_0603_1608Metric,C1644,2
1M47,R22,R_0603_1608Metric,C407542,1
1N4148W,D6,D_SOD-123,C83528,1
1k,"R112,R113,R124,R135,R136,R166,R167,R179,R180,R3,R8",R_0603_1608Metric,C2441633,11
1n,C71,C_0603_1608Metric,C1588,1
1u,"C22,C33,C68,C70,C84",C_0603_1608Metric,C15849,5
2.2uH,"L2,L3,L4",L_Coilcraft_XAL4020-XXX,C3151182,3
200R,R1,R_0603_1608Metric,C2479157,1
200k,"R103,R149,R155,R40,R46,R62,R68,R72,R97",R_0603_1608Metric,C2484346,9
205338-0004,"J2,J3",Molex_Pico-Lock_205338-0004_1x04-1MP_P2.00mm_Horizontal,C916325,2
20k,R74,R_0603_1608Metric,C3962749,1
22u,"C27,C28,C31,C32,C37,C38,C45,C46,C54,C55,C59,C72,C73",C_1210_3225Metric,C21397,13
27R,"R4,R5",R_0603_1608Metric,C2479456,2
2k7,"R121,R130,R142,R161,R173,R76,R77",R_0603_1608Metric,C237112,7
2u2,C11,C_0603_1608Metric,C57895,1
3n3,"C36,C44,C53",C_0603_1608Metric,C1613,3
49k9,R120,R_0603_1608Metric,C134320,1
4k7,"R105,R110,R133,R164,R177",R_0603_1608Metric,C4293273,5
4u7,"C12,C13,C14,C26",C_0805_2012Metric,C98192,4
5k1,"R16,R17",R_0603_1608Metric,C2484686,2
61k9,"R27,R48",R_0603_1608Metric,C2479523,2
680R,"R101,R147,R153,R38,R44,R60,R66,R95",R_0603_1608Metric,C844802,8
73k2,R70,R_0603_1608Metric,C843966,1
ABM8-272-T3,Y1,Crystal_SMD_3225-4Pin_3.2x2.5mm,C20625731,1
AOTA-B201610S3R3-101-T,L1,L_0806_2016Metric,C42411119,1
AP22653A,U14,DFN-6-1EP_2x2mm_P0.65mm_EP1x1.6mm,C5370049,1
APS6404L-3SQRx-SN,U2,SOIC-8_3.9x4.9mm_P1.27mm,C5333729,1
ASM330LHHG1TR,U22,LGA-14_3x2.5mm_P0.5mm_LayoutBorder3x4y,C26562099,1
BAT-HLD-012-SMT,BT2,BatteryHolder_LINX_BAT-HLD-012-SMT,C5189234,1
BAT54W,D14,SOT-323_SC-70,C153738,1
DMC3060LVT,Q2,TSOT-23-6,C5245242,1
DMP3056L,Q3,SOT-23,C150724,1
INA226-Q1,"U12,U7,U9",TSSOP-10_3x3mm_P0.5mm,C2653835,3
IRLML2803,Q1,SOT-23,C2590,1
LED_G_0603_LTST-C190GKT,"D11,D13,D15,D16,D17,D18,D4,D5,D7,D8",LED_0603_1608Metric,C125093,10
LTC4412xS6,U5,TSOT-23-6,C514442,1
MBT2222ADW1T1,"Q10,Q12,Q13,Q14,Q16,Q20,Q22,Q4,Q6,Q8",SOT-363_SC-70-6,C559075,10
MMBT2907,"Q18,Q19,Q24,Q25",SOT-23,C40752,4
MMC5983MA,U20,LGA-16_3x3mm_P0.5mm,C404329,1
NX3008NBKS,"Q11,Q15,Q17,Q21,Q23,Q5,Q7,Q9",SOT-363_SC-70-6,C396098,8
PTS647,"SW1,SW2",SW_SPST_PTS647_Sx38,C2689502,2
QSH-030-01-L-D-A,J14,SAMTEC_QSH-030-01-L-D-A,C2909821,1
QTH-030-01-L-D-A,J15,SAMTEC-QTH-030-01-X-D-A,C2843756,1
RP2350-B,U1,RP2350-QFN-80-1EP_10x10_P0.4mm_EP3.4x3.4mm_ThermalVias,C42415655,1
RV-3032-C7,U18,IC_RV-3032-C7-32.768KHZ-2.5PPM-TA-QC,C5366550,1
SMAJ9.0AHR3G,D3,D_SMA,C3720382,1
TPS22917DBV,"U17,U19,U21",SOT-23-6,C2680344,3
TPS3435AFACADDFRQ1,U4,TSOT-23-8,C33648053,1
TPS62902QRYTRQ1,"U10,U6,U8",TPS62902QRYTRQ1,C22445520,3
TPS7A52-Q1,U11,TPS7A5201Q,C523802,1
USB4105-GF-A,J1,USB_C_Receptacle_GCT_USB4105-xx-A_16P_TopMnt_Horizontal,C3020560,1
USBLC6-2SC6,D2,SOT-23-6,C7519,1
W25Q32JVSNIQ,U3,DFN-8-1EP_6x5mm_P1.27mm_EP2x2mm,C5355146,1
WS2812B,D1,LED_WS2812B_PLCC4_5.0x5.0mm_P3.2mm,C52917433,1
2k23,R85,R_0603_1608Metric,,1
MS621FE-FL11E,BT1,BatteryHolder_Seiko_MS621F,,1
60612202111308,J12,60612202111308,,1
60612202111308,J11,60612202111308,,1
TPS22992,U16,TPS22992,,1
E22P-433M30S,U13,E22-900M30S-SX1262,,1
PX1120S,U15,S1216_24PIN_PACKAGE,,1

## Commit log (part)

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2024-10-06 Added gitignore
2024-10-06 Initial commit of v1
2024-10-08 temp
2024-10-10 v1 done
2024-10-10 Updated i2c device addresses and mcu caps
2024-10-10 Added extra connector
2024-10-10 Silkscreen hiding
2024-10-22 Updated connector locations
2024-10-22 Fixed schematic bugs and corresponding layout modifications
2024-10-23 Updated connector locations and types
2024-10-23 Exported step
2024-10-23 Not sure what wasn't pushed
2024-10-24 Added silkscreen
2024-10-25 Minor fixes, export BOM
2024-10-25 Added footprints and reexported STEP
2024-11-16 Added better protection to SD card, Jetson IO, and added address breakouts to power monitors
2024-11-16 Added extra decoupling caps to LoRa
2024-11-19 Updated version to v2.1
2024-11-19 Fix gitignore tracking
2024-11-19 Moved csv bom
2024-11-19 Removed submodule KiCad-Libraries
2024-11-19 Re-add Kicad-libraries
2024-11-19 Stuff
2025-01-08 v3 partial schematic updates
2025-01-27 Updated IMU layout
2025-02-26 v3 Layout complete
2025-02-28 Addressed design issues
2025-04-02 Added BMX 160 interface board
2025-04-03 Updated board
2025-06-16 v4.0 Updates
2025-06-17 DFM updates
2025-06-17 Minor schematic fixes
2025-06-18 Fixed Jetson FPC pinout
2025-10-24 Update KiCad libraries
2025-10-24 updated watchdog
2025-10-26 Updated WDT
2025-10-27 Updated silkscreen
2026-01-07 v4.2 Updates
2026-01-21 kicad pull
2026-02-09 Updated BOM CSV
